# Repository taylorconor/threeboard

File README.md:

# threeboard

threeboard is a fully-functional open source and open hardware mechanical USB computer keyboard with only three keys. It supports multiple programmable layers, and achieves the same functionality as a full-sized keyboard. Its firmware and hardware are built completely from scratch and are extensively documented.

Unlike a traditional keyboard, characters don't show up on the screen after each keypress, because there aren't enough keys. Instead, combinations of the three keys are used to specify key and modifier codes on two built-in 8-bit LED binary indicators. This can then be sent to the host computer as USB keycodes. The multiple layers allow users to program macros into the threeboard’s storage for quick retrieval. All functionality is documented in the [threeboard user manual](documentation/threeboard/threeboard_user_manual.md).

## Motivation
The main goal of the threeboard project is to build a relatively easy to understand, readable, self-contained and well-documented embedded software and hardware project. The threeboard is built from scratch, with no external dependencies. This means that all components, from the USB stack to the PCB hardware designs, are written from the ground up and are all contained in this repository.

The threeboard project is extensively documented: within the firmware itself as comments, in this set of detailed markdown documents, and in a [PDF design document](documentation/threeboard_design_doc.pdf). The primary design goal of the C++ firmware code is readability, to enable as many people to read and learn from it as possible, regardless of background. It's well tested, including end-to-end integration tests which execute tests against the firmware in a hardware simulator to emulate the physical hardware.

## How to try it out

The threeboard project includes a terminal-based graphical firmware simulator capable of simulating the entire functionality of the threeboard. You can build and run the simulator yourself by reading the [simulator build instructions](documentation/threeboard/simulator_build_instructions.md). The simulator is built on top of the [simavr](https://github.com/buserror/simavr) AVR simulator, and runs the exact same firmware file that gets flashed to physical hardware. The simulator also allows remote debugging with GDB, so you can step through the threeboard firmware as it's being simulated to learn about it or investigate bugs!

Building your own physical threeboard requires a physical threeboard PCB, soldering tools and components, as well as some knowledge of electronics and soldering. If you're interested in building one, check out the [threeboard hardware build instructions](documentation/threeboard/hardware_build_instructions.md).

## Full documentation
Below are markdown files documenting various aspects of the threeboard project in detail. Full 41-page documentation is available in PDF format in the [threeboard design doc](documentation/threeboard_design_doc.pdf) file.

### Background reading 
[threeboard user manual](documentation/threeboard/threeboard_user_manual.md)  
[How do USB keyboards work?](documentation/threeboard/how_usb_keyboards_work.md) 

### Firmware
[Firmware design](documentation/threeboard/firmware_design.md)  
[Firmware build instructions](documentation/threeboard/firmware_build_instructions.md)  
[Simulator user manual & design](documentation/threeboard/simulator_manual_and_design.md)  
[Simulator build instructions](documentation/threeboard/simulator_build_instructions.md)  

### Hardware
[Hardware design](documentation/threeboard/hardware_design.md)  
[Hardware build instructions](documentation/threeboard/hardware_build_instructions.md)  
[Component list](documentation/threeboard/component_list.md)

Hardware designs are licensed under [CERN-OHL-P](hardware/LICENSE.txt), the firmware is licensed under [GPLv3](firmware/LICENSE.txt), and all documentation under [CC BY-SA 4.0](documentation/threeboard/LICENSE.txt).

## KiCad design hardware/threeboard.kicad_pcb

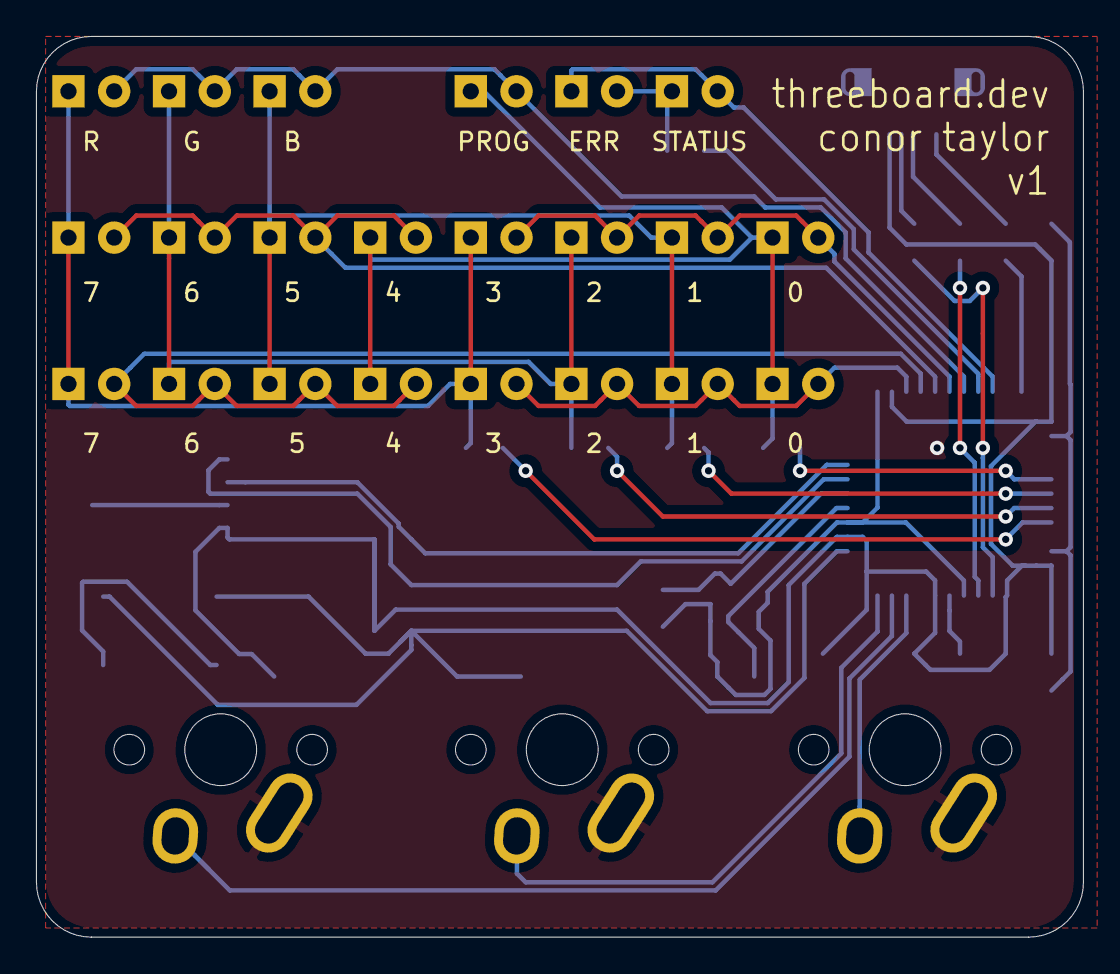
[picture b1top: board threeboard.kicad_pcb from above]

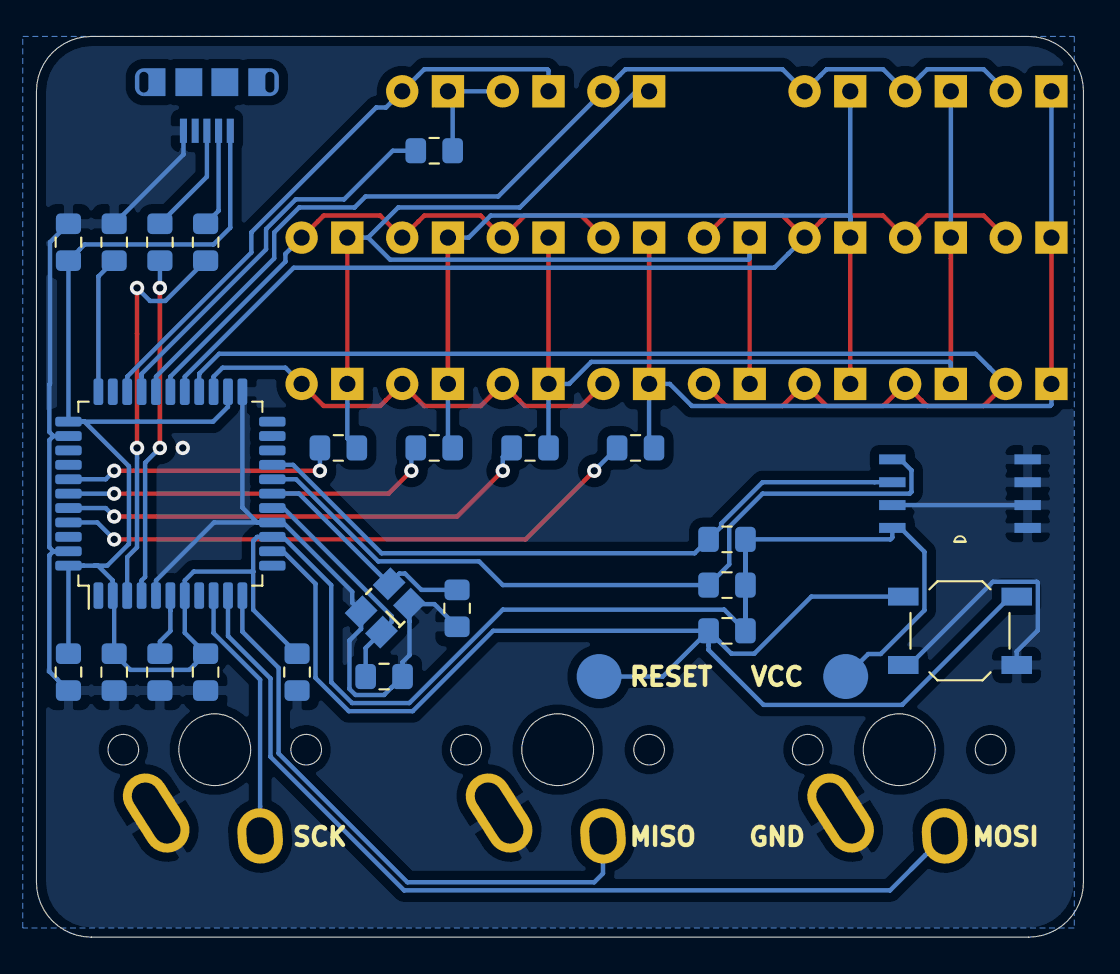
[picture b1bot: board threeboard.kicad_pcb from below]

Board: 2 copper layers, 58.2 x 50.0 mm, 49 parts (24 on the bottom side), 32 nets.

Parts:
0, 0#2, 1, 1#2, 2, 2#2, 3, 3#2, 4, 4#2, 5, 5#2, 6, 6#2, 7, 7#2: LED; LED_D3.0mm
B: LED; LED_D3.0mm
C1, C2: 22p; C_0805_2012Metric_Pad1.15x1.40mm_HandSolder
C3, C4, C5, C6: 0.1u; C_0805_2012Metric_Pad1.15x1.40mm_HandSolder
C7: 4.7u; C_0805_2012Metric_Pad1.15x1.40mm_HandSolder
C8: 1u; C_0805_2012Metric_Pad1.15x1.40mm_HandSolder
ERR: LED; LED_D3.0mm
G: LED; LED_D3.0mm
J1: USB_mini_micro_B; AMPHENOL_10118194-0001LF
K1, K2, K3: KEYSW; Mx_Alps_100
PROG: LED; LED_D3.0mm
R: LED; LED_D3.0mm
R1, R2: 10k; R_0805_2012Metric_Pad1.15x1.40mm_HandSolder
R3, R4: 22; R_0805_2012Metric_Pad1.15x1.40mm_HandSolder
R5, R6, R7, R8, R9: 220; R_0805_2012Metric_Pad1.15x1.40mm_HandSolder
R10, R11: 4.7k; R_0805_2012Metric_Pad1.15x1.40mm_HandSolder
STATUS: LED; LED_D3.0mm
SW1: SW_PUSH; SW_SPST_TL3342
U1: ATMEGA32U4; LQFP-44_10x10mm_P0.8mm
U2: 24LC512; SOIC127P794X203-8N
X1: XTAL_GND; crystal_FA238-TSX3225

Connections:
/col0: R5.2, U1.41
/col1: R6.2, U1.40
/col2: R7.2, U1.39
/col3: R8.2, U1.38
/eeprom_scl: R11.2, U1.19, U2.6
/eeprom_sda: R10.2, U1.18, U2.5
/row0: 4.2, 5.2, 6.2, 7.2, U1.27
/row1: 0.2, 1.2, 2.2, 3.2, U1.28
/row2: 4#2.2, 5#2.2, 6#2.2, 7#2.2, U1.26
/row3: 0#2.2, 1#2.2, 2#2.2, 3#2.2, U1.25
/row4: B.2, G.2, PROG.2, R.2, U1.29
/status0: R9.2, U1.30
/status1: ERR.1, STATUS.2, U1.31
/switch1: K1.2, U1.10
/switch2: K2.2, U1.11
/switch3: K3.2, U1.9
GND: C1.2, C2.2, C3.2, C4.2, C5.2, C6.2, C7.2, C8.2, J1.5, K1.1, K2.1, K3.1, R2.1, SW1.1, U1.5, U1.15, U1.23, U1.35, U1.43, U2.1, U2.2, U2.3, U2.4, U2.7, X1.3
unnamed: C1.1, U1.16, X1.1
unnamed: C2.1, U1.17, X1.2
unnamed: C8.1, U1.6
unnamed: 3.1, 3#2.1, 7.1, 7#2.1, R.1, R5.1
unnamed: 2.1, 2#2.1, 6.1, 6#2.1, G.1, R6.1
unnamed: 1.1, 1#2.1, 5.1, 5#2.1, B.1, R7.1
unnamed: 0.1, 0#2.1, 4.1, 4#2.1, PROG.1, R8.1
unnamed: ERR.2, R9.1, STATUS.1
unnamed: J1.2, R3.2
unnamed: J1.3, R4.2
unnamed: R1.2, SW1.2, U1.13
unnamed: R2.2, U1.33
unnamed: R3.1, U1.3
unnamed: R4.1, U1.4
VCC: C3.1, C4.1, C5.1, C6.1, C7.1, J1.1, R1.1, R10.1, R11.1, U1.2, U1.7, U1.14, U1.24, U1.34, U1.44, U2.8

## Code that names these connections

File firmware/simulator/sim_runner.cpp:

#include "sim_runner.h"

#include "sim_ui.h"
#include <iostream>

namespace threeboard {
namespace simulator {
namespace {
using namespace std::placeholders;

// Used to test a single pin in a register.
bool IsEnabled(uint8_t reg, uint8_t pin) { return reg & (1 << pin); }

} // namespace

SimRunner::SimRunner() { simulator_ = std::make_unique<Simulator>(); }

void SimRunner::RunSimulator() {
  if (sim_ui_ != nullptr) {
    std::cout << "Attempted to run a running simulator instance!" << std::endl;
    exit(0);
  }
  simulator_->Reset();
  simulator_->RunAsync();
  sim_ui_ = std::make_unique<SimUI>(
      std::bind(&SimRunner::UpdateSimState, this),
      std::bind(&SimRunner::HandleKeypress, this, _1, _2),
      simulator_->GetState(), simulator_->GetCycleCount());
  sim_ui_->StartRenderLoopAsync();
  std::unique_lock<std::mutex> lock(mutex_);
  cond_var_.wait(lock);
  sim_ui_ = nullptr;
}

void SimRunner::UpdateSimState() {
  uint8_t portb = simulator_->GetPortB();
  uint8_t portc = simulator_->GetPortC();
  uint8_t portd = simulator_->GetPortD();
  uint8_t portf = simulator_->GetPortF();

  // Clear the LED state before the next frame is calculated.
  sim_ui_->ClearLedState();

  // The ERR/STATUS LED pair for threeboard v1 is wired as follows:
  // status0: PB6, ERR
  // status1: PC6, STATUS
  if (IsEnabled(portb, 6) && !IsEnabled(portc, 6)) {
    sim_ui_->SetErr(true);
  } else if (IsEnabled(portc, 6) && !IsEnabled(portb, 6)) {
    sim_ui_->SetStatus(true);
  }

  // The wiring of the LED matrix for threeboard v1 is detailed below. Scanning
  // is row-major, meaning only one row is active at a time. The column pins
  // can be effectively considered as active low.
  // row0: PD7, B0_{4,5,6,7}
  // row1: PB4, B0_{0,1,2,3}
  // row2: PD6, B1_{4,5,6,7}
  // row3: PD4, B1_{0,1,2,3}
  // row4: PB5, (R, G, B, PROG)
  // col0: PF0, (R, B0_3, B0_7, B1_3, B1_7)
  // col1: PF1, (G, B0_2, B0_6, B1_2, B1_6)
  // col2: PF4, (B, B0_1, B0_5, B1_1, B1_5)
  // col3: PF5, (PROG, B0_0, B0_4, B1_0, B1_4)
  if (IsEnabled(portd, 7)) {
    sim_ui_->SetBank0(!IsEnabled(portf, 0), 7);
    sim_ui_->SetBank0(!IsEnabled(portf, 1), 6);
    sim_ui_->SetBank0(!IsEnabled(portf, 4), 5);
    sim_ui_->SetBank0(!IsEnabled(portf, 5), 4);
  } else if (IsEnabled(portb, 4)) {
    sim_ui_->SetBank0(!IsEnabled(portf, 0), 3);
    sim_ui_->SetBank0(!IsEnabled(portf, 1), 2);
    sim_ui_->SetBank0(!IsEnabled(portf, 4), 1);
    sim_ui_->SetBank0(!IsEnabled(portf, 5), 0);
  } else if (IsEnabled(portd, 6)) {
    sim_ui_->SetBank1(!IsEnabled(portf, 0), 7);
    sim_ui_->SetBank1(!IsEnabled(portf, 1), 6);
    sim_ui_->SetBank1(!IsEnabled(portf, 4), 5);
    sim_ui_->SetBank1(!IsEnabled(portf, 5), 4);
  } else if (IsEnabled(portd, 4)) {
    sim_ui_->SetBank1(!IsEnabled(portf, 0), 3);
    sim_ui_->SetBank1(!IsEnabled(portf, 1), 2);
    sim_ui_->SetBank1(!IsEnabled(portf, 4), 1);
    sim_ui_->SetBank1(!IsEnabled(portf, 5), 0);
  } else if (IsEnabled(portb, 5)) {
    sim_ui_->SetR(!IsEnabled(portf, 0));
    sim_ui_->SetG(!IsEnabled(portf, 1));
    sim_ui_->SetB(!IsEnabled(portf, 4));
    sim_ui_->SetProg(!IsEnabled(portf, 5));
  }
  return;
}

void SimRunner::HandleKeypress(SimUI::Key key, bool state) {
  if (key == SimUI::Key::KEY_Q) {
    cond_var_.notify_all();
    return;
  }

  // The key pins are all active low.
  if (key == SimUI::Key::KEY_A) {
    // Switch 1 - maps to PB2.
    simulator_->SetPinB(2, !state);
  } else if (key == SimUI::Key::KEY_S) {
    // Switch 2 - maps to PB3.
    simulator_->SetPinB(3, !state);
  } else if (key == SimUI::Key::KEY_D) {
    // Switch 3 - maps to PB1.
    simulator_->SetPinB(1, !state);
  }
}
} // namespace simulator
} // namespace threeboard

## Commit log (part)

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2019-12-28 Add initial files
2020-01-02 Add FSM and event handling
2020-01-05 Add extra tests
2020-01-20 Add USB HID implementation
2020-01-23 Add USB HID implementation 2
2020-01-24 Add USB HID implementation 4
2020-01-27 Add USB HID implementation 5
2020-01-27 Add USB HID implementation 6
2020-01-27 Add USB HID implementation 7
2020-01-30 Add USB HID implementation 9
2020-01-31 Convert defines to constexpr
2020-02-11 Add threeboard v1 schema
2020-02-11 Add initial i2c implementation
2020-02-16 Move USB-internal packages to internally visibile directory
2020-02-16 Refactor native constants into separate file
2020-02-16 Refactor KeypressHandlerDelegate into its own file
2020-02-18 Add test for key_controller
2020-02-18 Refactor delegates into subdirectory
2020-02-18 Make Native::Delay use a more accurate busyloop
2020-02-19 Make remaining USB targets compile for x86 too.
2020-02-22 Add initial USB test
2020-02-24 Add initial USB integration test (unfinished)
2020-02-27 Use StrictMock everywhere by default
2020-03-22 Refactor bazel rules and BUILD files
2020-03-22 Add basic documentation for avr toolchain
2020-04-02 Add v1 hardware revision with reinforced USB, better LED placement, and dual SMD EEPROM
2020-04-22 Add initial BUILD wiring for simavr
2020-04-22 Migrate bazel avr toolchain to separate repo
2020-04-25 Add initial simulator binary
2020-04-28 Add support for atmega32u4 core in the simulator
2020-05-20 Add simulator terminal UI and wire it up to the simulated firmware
2020-05-23 Update README and documentation structure
2020-05-23 Remove unnecessary WORKSPACE declarations
2020-05-28 Make the project platform-independent to compile on macOS and Linux, and add .travis.yml config
2020-05-28 Fix travis config validation warnings
2020-06-04 Fix key registering issue
2020-06-19 Refactor simulator UI to communicate via a simulator delegate
2020-07-26 Add debugging capabilities to the simulator
2020-07-27 Small fixes
2020-09-12 Begin USB simulation work (still not complete)
2020-09-17 Add USB host simulation
2020-09-18 Code reformatting
2020-09-19 Refactor firmware state changes into a new delegate
2020-09-20 Migrate simulator components to their own package and refactor BUILD file formatting
2020-09-21 Add TODO list
2020-09-26 Refactor simavr code behind a shim interface to enable testing and isolation
2020-10-03 Add logging class to enable logging from the firmware to the simulator when running simulated.
2020-10-04 Surface USB status in the simulator UI
2020-10-10 Add memory usage breakdown view to the simulator
2020-10-10 Add avr-libc manual
2020-10-10 Add USB keyboard output to the simulator UI
2020-10-11 Refactor pad title rendering to the pad class
2020-10-18 Add initial simulated eeprom, add lifetime support to simavr interface
2020-10-18 Add testing boilerplate files and mocks for simulator/components
2020-10-18 Add test template for logging class
2020-10-23 Remove unnecessary dependency
2020-10-27 Add initial i2c eeprom code, still needs refactoring into native
2021-01-31 Move I2C config into the simavr interface.
    Also do some initial general refactoring. More to follow.
2021-02-01 Fix imports for Linux build
2021-02-01 Update main README
2021-02-04 Refactor led_controller to remove use of bitset
2021-02-05 Update led_controller comments
2021-02-05 Add documentation outline
2021-02-07 Write the threeboard user manual
2021-02-07 Fix build error
2021-02-08 Fix construction order
2021-02-12 Add layer interface and migrate threeboard class to use it
2021-02-12 Add some clang-tidy fixes
2021-02-13 Add LayerController interface
2021-02-13 Rename Run to RunEventLoop
2021-02-20 Add .clang-format config
2021-02-21 Add new hardware documentation images
2021-02-21 Add more hardware documentation images
2021-02-28 Add remaining hardware documantation images
2021-03-04 Fix clang-format file to use version 10.0.0-4ubuntu1
2021-03-04 Add LedState to restrict access to the LedController from the Layers
2021-03-06 Refactor KeypressEventHandler into a generic EventHandler
2021-03-06 Remove magic number from USB stack
2021-03-07 Remove testonly setter in UsbImpl
2021-03-08 Add ErrorHandlerDelegate and initial error handling
2021-03-11 Improve USB stack error handling
2021-03-11 Correctly verify USB frame number
2021-03-14 Add comments to USB constants
2021-03-15 Add WAIT_OR_RETURN macro to simplify USB polling
2021-03-16 Make USB PLL lock error message more specific
2021-03-16 Add hardware scan to documentation image set
2021-04-04 Fix build breakage
2021-04-04 Add local .bazelrc with C++ version info
2021-04-04 Install curses during Travis linux installer phase
2021-04-04 Improve LedController test coverage
2021-04-04 Add simulator screenshot
2021-04-04 Add tests for Logging class
2021-04-04 Add initial files and mocks for ThreeboardTest
2021-04-06 Add constructor expectations to ThreeboardTest
2021-04-07 Add tests for Threeboard class
2021-04-09 Add some UsbImpl tests
2021-04-20 Add boot indicator LED sequence
2021-04-20 Switch ERR and STATUS LED placement to match hardware v1
2021-04-20 Zero initialise boot_indicator_state
2021-04-20 Update USB Setup timer
2021-04-24 Remove temporary i2c code
2021-04-24 Move i2c class to new storage directory
2021-04-26 Add internal EEPROM class and associated EEPROM interface
2021-04-26 Add skeleton storage_controller class
2021-05-15 Remove unused TWI ISR
2021-05-15 Remove NativeImpl getter
2021-05-15 Wire up the StorageController into the Threeboard class
2021-05-15 Bump avr-bazel
2021-05-15 Fix SimulatorDelegateMock
2021-05-15 Rename Usb to UsbController
2021-05-15 Fix cppcheck issues
2021-05-15 Make NativeImpl final, move the static instance pointer to impl file
2021-05-23 Add initial integration test setup
2021-05-23 Move third_party directory to top level
2021-05-23 Fix include files
2021-05-23 Temporary fix for macOS linker issue in sim_test
2021-05-23 Fix simavr firmware dependency
2021-05-23 Add SimulatedTestBase
2021-05-23 Move simulator binary definition to simavr_impl
2021-05-23 Implement working BootToEventLoop test
2021-05-23 Finalize classes by default
2021-05-30 Add initial integrity checks for integration tests
2021-06-01 Add InstrumentingSimavr
2021-06-01 Improve InstrumentingSimavr performance
2021-06-02 Remove heap pointer modifiers that were causing UB
2021-06-02 Small performance improvements for InstrumentingSimavr
2021-06-02 Remove ubsan from default test flags
2021-06-02 Propagate StorageController to relevant layers
2021-06-02 Implement initial LayerR logic
2021-06-03 Move StorageController ownership to relevant derived Layer classes
2021-06-06 Add simulator-specific logging macros
2021-06-15 Remove unnecessary include
2021-06-15 Fix simulator logging to add logs to log file
2021-07-08 Working EEPROM simulation implementation
2021-07-08 Remove SymbolInfo hack from integration test suite
2021-07-11 Add PULSE mode for LEDs
2021-07-17 Implement word shortcut logic
2021-07-17 Fix GCC issue with LedState bitfield
2021-07-18 Fix simulator logging includes for linux
2021-07-23 Propagate errors from TransitionedToLayer
2021-07-24 Increase prescaler value for timer 3
2021-07-25 Update Bazel rules to remove warnings
2021-07-25 Add logging hook for simavr logs to display in the threeboard simulator log file
2021-08-04 Fix GDB port overflow
2021-08-07 Assign to TCCR registers
2021-08-08 Add StateStorage class for managing persisted threeboard state on disk
2021-08-15 Remove unnecessary logging
2021-08-15 Fix off-by-one issue for Layer G size
2021-08-17 Add layer documentation images
2021-08-18 Complete word modification implementation for layer G
2021-08-20 Add blob shortcut interface to StorageController
2021-08-20 Increase test coverage for threeboard.cpp
2021-08-21 Add tests for LayerController
2021-08-21 Add tests for DefaultLayer
2021-08-21 Add tests for Layer R
2021-08-21 Add stub test files for layers G and B
2021-08-21 Add Layer R test for YZ prog keycode
2021-08-21 Add tests for Layer::TransitionToLayer
2021-08-22 Small comment fixes
2021-08-22 Fix compilation issue in InstrumentingSimavr
2021-08-22 Fix integration test crash
2021-08-23 Refactor Keypress into a standalone header
2021-08-25 Add initial ThreeboardModel
2021-09-05 Refactor UI to run the Simulator
2021-09-05 Finalize refactored simulator components
2021-09-05 Refactor Simulator interface
2021-09-06 Add initial failing property-based test
2021-09-06 Rename keypress_generator
2021-09-07 Fix Simulator configuration for property test
2021-09-12 Stability refactoring for the Simulator
2021-09-13 Add Layer R property test
2021-09-15 Add property tests for Layer G
2021-09-15 Remove fast run mode
2021-09-16 Allow pausing Simulator during atomic blocks
2021-09-18 Move symbol table to InstrumentingSimavr
2021-09-27 Allow disabling of instrumentation recording in InstrumentingSimavr
2021-09-27 Speed up boot indicator
2021-09-27 Improve symbol parsing and error messages
2021-09-27 Add timer interrupt verification integration test
2021-10-01 Fix simulator logging to file
2021-10-10 Add support for missing state storage files
2021-10-10 Add intellij .idea to .gitignore
2021-10-11 Update TODO
2021-10-11 Move ownership of simulator EEPROMs to StateStorage
2021-10-11 Handle default StateStorage case
2021-10-30 Make integration tests fast and stable enough to enable.
2021-10-31 Use fake StateStorage implementation in simulator tests
2021-10-31 Remove unused simulator pause option
2021-10-31 Only create log file when explicitly asked to
2021-11-02 Add operator<< to DeviceState for easy debugging
2021-11-02 Enable headless tests to run the firmware faster than realtime
2021-11-07 Decouple LayerGModel shortcut length from string length
2021-11-07 Correctly populate SimulatorState::usb_attached
2021-11-07 Split UsbHost into interface and impl
2021-11-07 Add Framework linking to bazelrc
2021-11-12 Fix model tetsting for nonprintable charactters in Layer G
2021-11-12 Fix buildability on Linux
2021-11-12 Add comments
2021-11-12 Remove unnecessary InstrumentingSimavr static method
2021-11-13 Clean up tests
2021-11-14 Remove unnecessary error_handler_delegate
2021-11-14 Implement Layer B business logic and tests
2021-11-15 Implement blob shortcut logic in the storage layer
2021-11-15 Add unimplemented StorageController test file
2021-11-18 Add property test support for Layer G
2021-11-20 Add StorageController test suite
2021-11-20 Remove stale docs
2021-11-21 Add user manual document
2021-11-23 Add simulator design documeent
2021-11-23 Update broken doc link
2021-11-23 Add hardware design documentation
2021-11-24 Fix markdown image alignment
2021-11-24 Move component list to its own document
2021-11-24 Further compress PCB scan image
2021-11-24 Fix size and alignment of images
2021-11-26 Add firmware and simulator build instructions
2021-11-26 Rename simulator design document
2021-12-05 Add TODOs for unfinished markdown documents
2021-12-24 Add hardware build instructions document
2021-12-25 Fix USB keycode rendering bug
2021-12-25 Add new simulator video to README
2021-12-25 Remove duplicated manufacturing section
2021-12-25 Fix documentation spelling errors
2021-12-26 Compress all documentation pngs
2021-12-30 Update USB documentation
2021-12-30 Add 'how usb keyboards work' document
2021-12-30 Remove README todo
2021-12-30 Add full design doc PDF
2021-12-30 Fix documentation issue
2021-12-31 Create CNAME
2021-12-31 Fix design doc pdf
2021-12-31 Rename design doc pdf
2021-12-31 Add small images for USB connectors
2021-12-31 Refactor firmware design doc for Pages
2021-12-31 Refactor hardware design doc for Pages
2021-12-31 Refactor hardware build instructions doc for Pages
2021-12-31 Final PNG compression pass
2021-12-31 Compress simulator gif
2021-12-31 Add GitHub Pages index.html
2021-12-31 Add link to index.html
2021-12-31 Remove GitHub Pages artefacts from master branch
2021-12-31 Fix corner rounding on gif
2021-12-31 Remove unused border-radius from gif
2022-01-01 Add custom link to all GitHub Pages pages
2022-01-01 Remove unused Native methods
2022-01-01 Remove unused test files
2022-01-01 Remove obsolete TODOs
2022-01-01 Refactor header file comments
2022-01-01 Refactor obsolete todos
2022-01-11 Add LICENSE files
